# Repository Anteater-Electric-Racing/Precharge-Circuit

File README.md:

# [Schematic Preview](https://kicanvas.org/?github=https%3A%2F%2Fgithub.com%2FAnteater-Electric-Racing%2FPrecharge-Circuit%2Fblob%2Fmain%2Fpcc_v0.1.kicad_sch)

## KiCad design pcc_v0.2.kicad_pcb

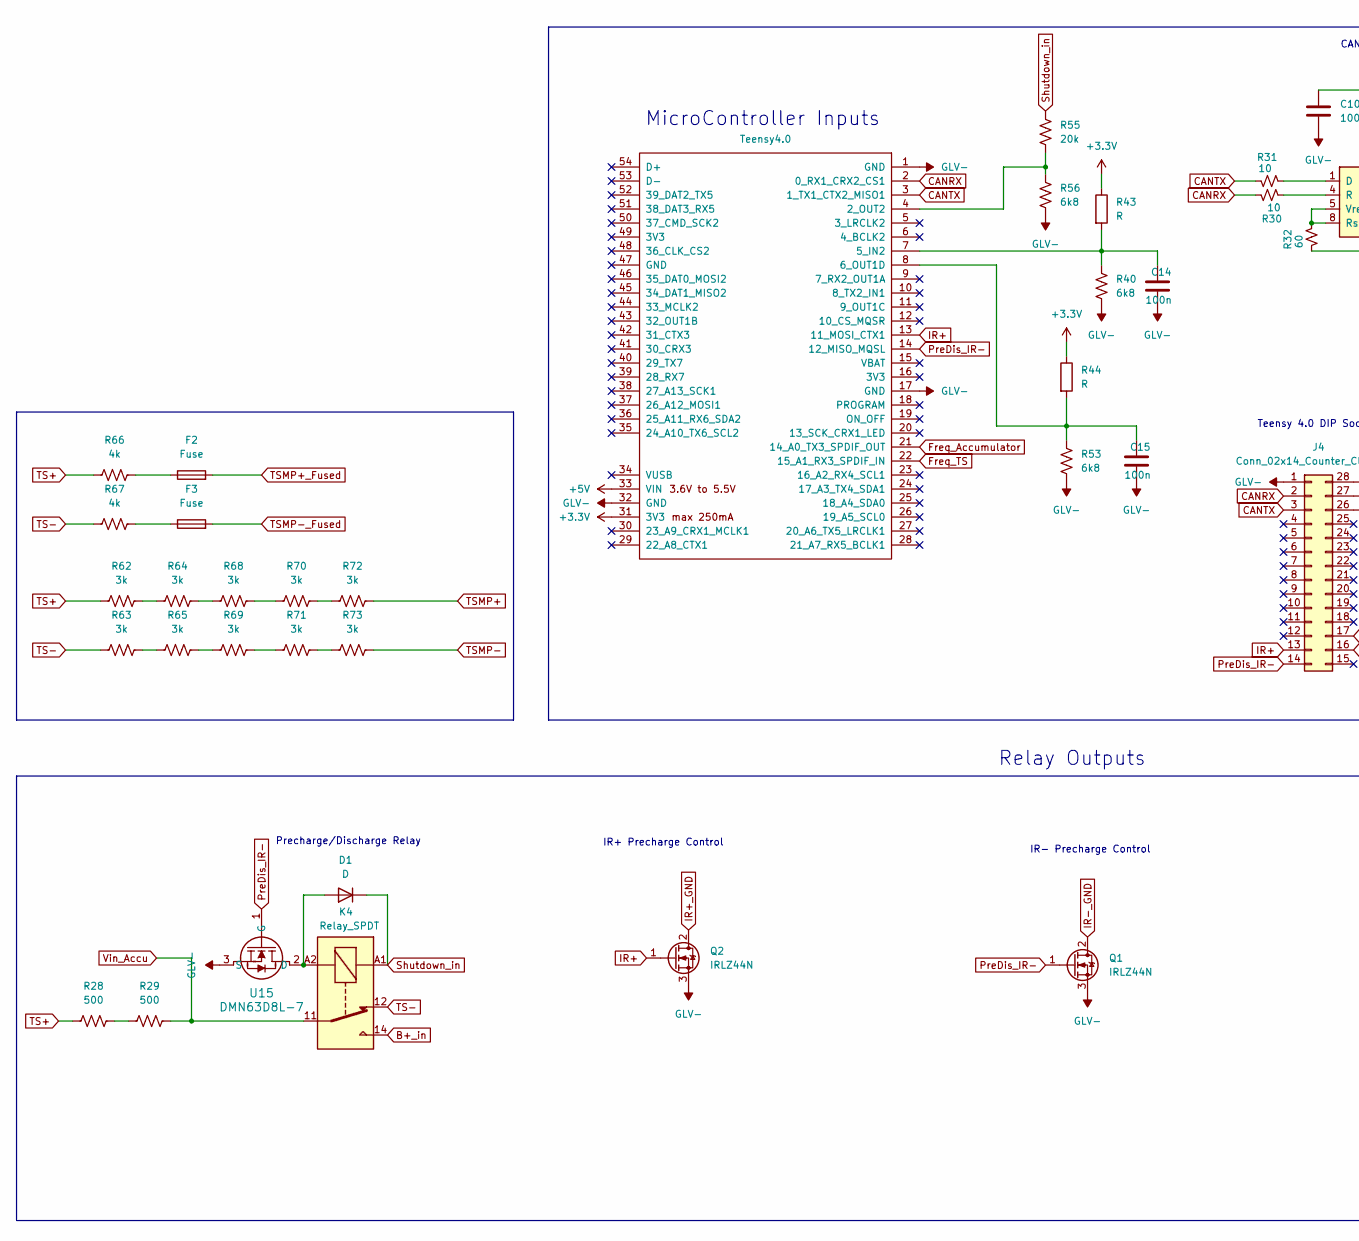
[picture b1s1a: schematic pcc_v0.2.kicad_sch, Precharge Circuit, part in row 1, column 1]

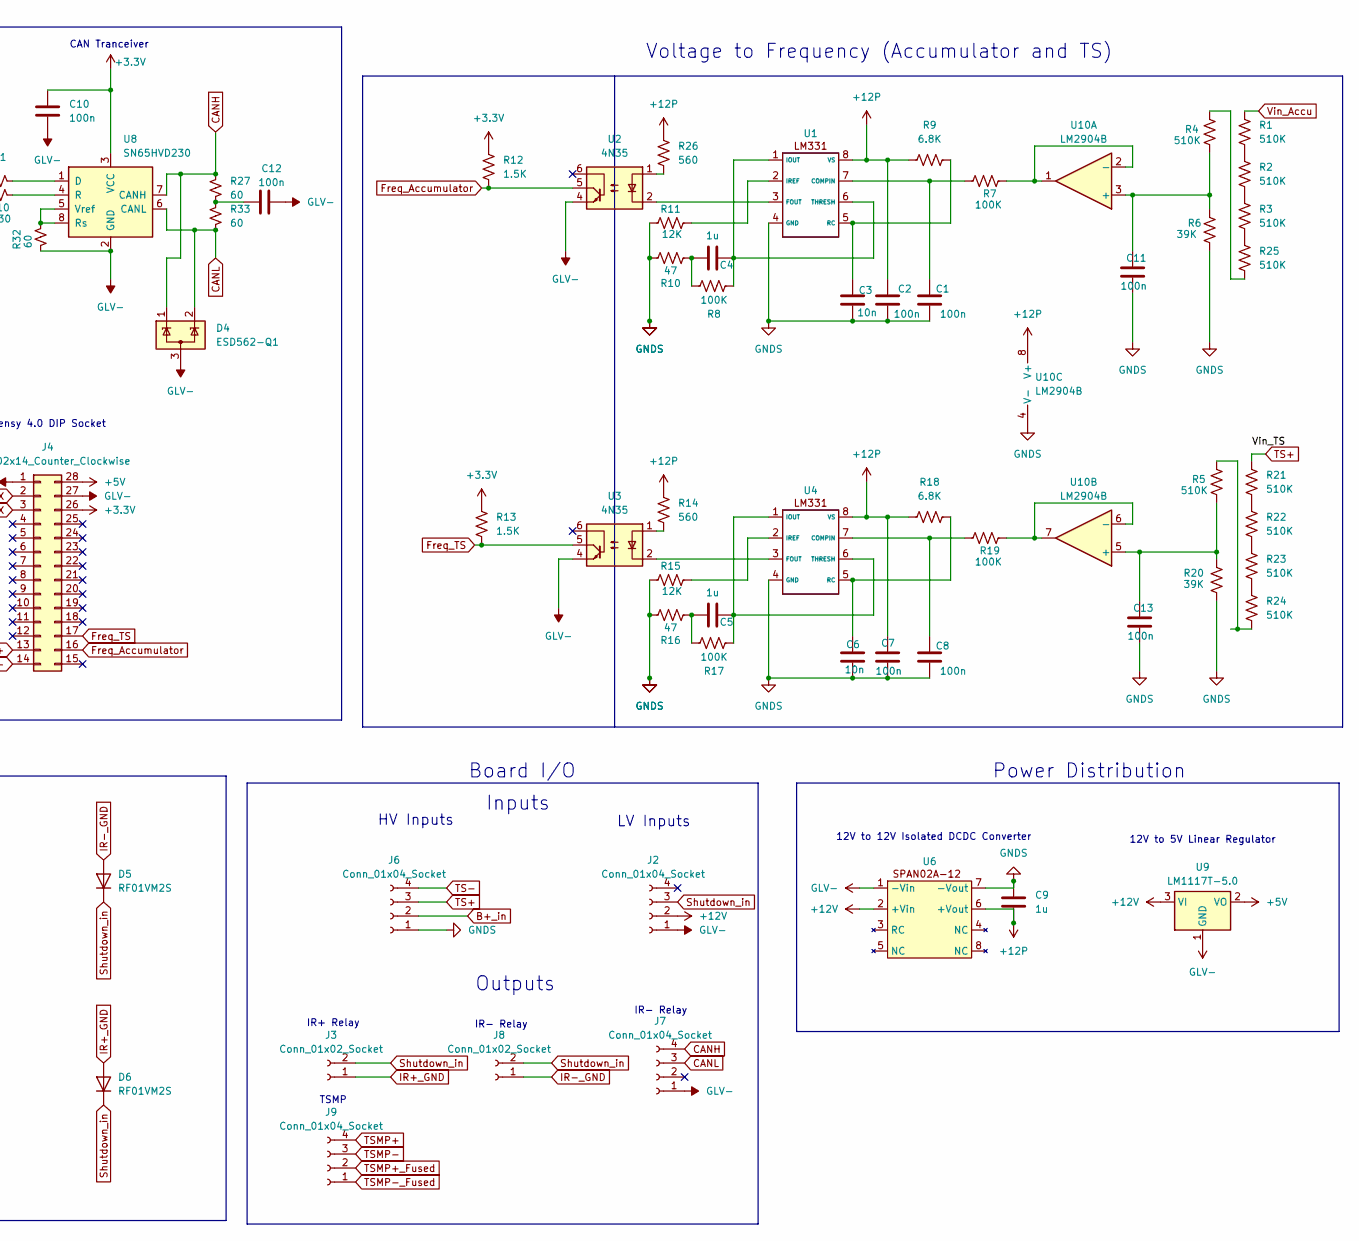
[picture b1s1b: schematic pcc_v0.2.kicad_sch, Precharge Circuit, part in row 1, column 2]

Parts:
C1, C2, C7, C8, C10, C11, C12, C13, C14, C15: 100n; C_0805_2012Metric
C3, C6: 10n; C_0805_2012Metric
C4, C5, C9: 1u; C_0805_2012Metric
D1: D; D_5KPW_P7.62mm_Vertical_AnodeUp
D4: ESD562-Q1; SOT-23-3
D5, D6: RF01VM2S; D_SOD-323
F2, F3: Fuse; Fuse_1206_3216Metric
J2, J6, J7, J9: Conn_01x04_Socket; Molex_Mini-Fit_Jr_5566-04A2_2x02_P4.20mm_Vertical
J3, J8: Conn_01x02_Socket; Molex_Mini-Fit_Jr_5566-02A2_2x01_P4.20mm_Vertical
J4: Conn_02x14_Counter_Clockwise; DIP-28_W15.24mm_Socket
K4: Relay_SPDT; Precharge_Discharge_Relay
Q1, Q2: IRLZ44N; TO-220-3_Vertical
R1, R2, R3, R4, R5, R21, R22, R23, R24, R25: 510K; R_0805_2012Metric
R6, R20: 39K; R_0805_2012Metric
R7, R8, R17, R19: 100K; R_0805_2012Metric
R9, R18: 6.8K; R_0805_2012Metric
R10, R16: 47; R_0805_2012Metric
R11, R15: 12K; R_0805_2012Metric
R12, R13: 1.5K; R_0805_2012Metric
R14, R26: 560; R_0805_2012Metric
R27, R32, R33: 60; R_0805_2012Metric
R28, R29: 500; Ohmite HS100 500R F
R30, R31: 10; R_0805_2012Metric
R40, R53, R56: 6k8; R_0805_2012Metric
R43, R44: R; PinSocket_1x02_P2.00mm_Vertical
R55: 20k; R_0805_2012Metric
R62, R63, R64, R65, R68, R69, R70, R71, R72, R73: 3k; R_2512_6332Metric
R66, R67: 4k; R_0805_2012Metric
U1, U4: DIP-8_W7.62mm_Socket
U2, U3: 4N35; DIP-6_W7.62mm_Socket
U6: SIP-8_19x3mm_P2.54mm
U7: Teensy4.0; DIP-28_W15.24mm_Socket
U8: SN65HVD230; SOIC-8_3.9x4.9mm_P1.27mm
U9: LM1117T-5.0; TO-220-3_Horizontal_TabDown
U10: LM2904B; SOIC-8_3.9x4.9mm_P1.27mm
U15: DMN63D8L-7; SOIC_63D8L-7_DIO

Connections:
+3.3V: C10.1, J4.26, R12.2, R13.2, R43.1, R44.1, U7.31 (3V3), U8.3 (VCC)
+5V: J4.28, U7.33 (VIN), U9.2 (VO)
+12P: C2.1, C7.1, C9.2, R9.1, R14.1, R18.1, R26.1, U1.8 (VS), U4.8 (VS), U6.6 (+Vout), U10.8 (V+)
+12V: J2.2, U6.2 (+Vin), U9.3 (VI)
B+_in: J6.2, K4.14
CANH: D4.1 (K), J7.4, R27.1, U8.7 (CANH)
CANL: D4.2 (K), J7.3, R33.2, U8.6 (CANL)
CANRX: J4.2, R30.1, U7.2 (0_RX1_CRX2_CS1)
CANTX: J4.3, R31.2, U7.3 (1_TX1_CTX2_MISO1)
Freq_Accumulator: J4.16, R12.1, U2.5, U7.21 (14_A0_TX3_SPDIF_OUT)
Freq_TS: J4.17, R13.1, U3.5, U7.22 (15_A1_RX3_SPDIF_IN)
GLV-: C10.2, C12.2, C14.2, C15.2, D4.3 (A), J2.1, J4.1, J4.27, J7.1, Q1.3 (S), Q2.3 (S), R32.2, R40.2, R53.2, R56.2, U2.4, U3.4, U6.1 (-Vin), U7.1 (GND), U7.17 (GND), U7.32 (GND), U8.2 (GND), U9.1 (GND), U15.3 (S)
GNDS: C1.2, C2.2, C3.2, C6.2, C7.2, C8.2, C9.1, C11.2, C13.2, J6.1, R6.2, R10.2, R11.1, R15.1, R16.2, R20.2, U1.4 (GND), U4.4 (GND), U6.7 (-Vout), U10.4 (V-)
IR+: J4.13, Q2.1 (G), U7.13 (11_MOSI_CTX1)
IR+_GND: D6.2 (A), J3.1, Q2.2 (D)
IR-_GND: D5.2 (A), J8.1, Q1.2 (D)
unnamed: C4.1, R8.1, R10.1
unnamed: C5.1, R16.1, R17.1
unnamed: C12.1, R27.2, R33.1
unnamed: C14.1, R40.1, R43.2, U7.7 (5_IN2)
unnamed: C15.1, R44.2, R53.1, U7.8 (6_OUT1D)
unnamed: D1.2 (A), K4.A2, U15.2 (D)
unnamed: F2.1, R66.1
unnamed: F3.1, R67.1
unnamed: R1.2, R2.1
unnamed: R2.2, R3.1
unnamed: R14.2, U3.1
unnamed: R21.2, R22.1
unnamed: R22.2, R23.1
unnamed: R23.2, R24.1
unnamed: R5.1, R24.2
unnamed: R3.2, R25.1
unnamed: R4.1, R25.2
unnamed: R26.2, U2.1
unnamed: R28.2, R29.1
unnamed: R55.2, R56.1, U7.4 (2_OUT2)
unnamed: R62.2, R64.1
unnamed: R63.2, R65.1
unnamed: R64.2, R68.1
unnamed: R65.2, R69.1
unnamed: R68.2, R70.1
unnamed: R69.2, R71.1
unnamed: R70.2, R72.1
unnamed: R71.2, R73.1
unnamed: C1.1, R7.1, U1.7 (COMPIN)
unnamed: U1.3 (FOUT), U2.2
unnamed: C4.2, R8.2, U1.1 (IOUT), U1.6 (THRESH)
unnamed: R11.2, U1.2 (IREF)
unnamed: C3.1, R9.2, U1.5 (RC)
unnamed: C8.1, R19.1, U4.7 (COMPIN)
unnamed: U3.2, U4.3 (FOUT)
unnamed: C5.2, R17.2, U4.1 (IOUT), U4.6 (THRESH)
unnamed: R15.2, U4.2 (IREF)
unnamed: C6.1, R18.2, U4.5 (RC)
unnamed: R31.1, U8.1 (D)
unnamed: R30.2, U8.4 (R)
unnamed: R32.1, U8.5 (Vref), U8.8 (Rs)
unnamed: C11.1, R4.2, R6.1, U10.3 (+)
unnamed: R7.2, U10.1, U10.2 (-)
unnamed: C13.1, R5.2, R20.1, U10.5 (+)
unnamed: R19.2, U10.6 (-), U10.7
PreDis_IR-: J4.14, Q1.1 (G), U7.14 (12_MISO_MQSL), U15.1 (G)
Shutdown_in: D1.1 (K), D5.1 (K), D6.1 (K), J2.3, J3.2, J8.2, K4.A1, R55.1
TS+: J6.3, R21.1, R28.1, R62.1, R66.2
TS-: J6.4, K4.12, R63.1, R67.2
TSMP+: J9.4, R72.2
TSMP+_Fused: F2.2, J9.2
TSMP-: J9.3, R73.2
TSMP-_Fused: F3.2, J9.1
Vin_Accu: K4.11, R1.1, R29.2

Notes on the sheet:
Board I/O
TSMP
HV Inputs
Inputs
IR+ Relay
LV Inputs
Teensy 4.0 DIP Socket
IR- Precharge Control
Voltage to Frequency (Accumulator and TS)
MicroController Inputs
IR- Relay
Relay Outputs
CAN Tranceiver
Precharge/Discharge Relay
IR+ Precharge Control
Outputs
Power Distribution
12V to 5V Linear Regulator
12V to 12V Isolated DCDC Converter

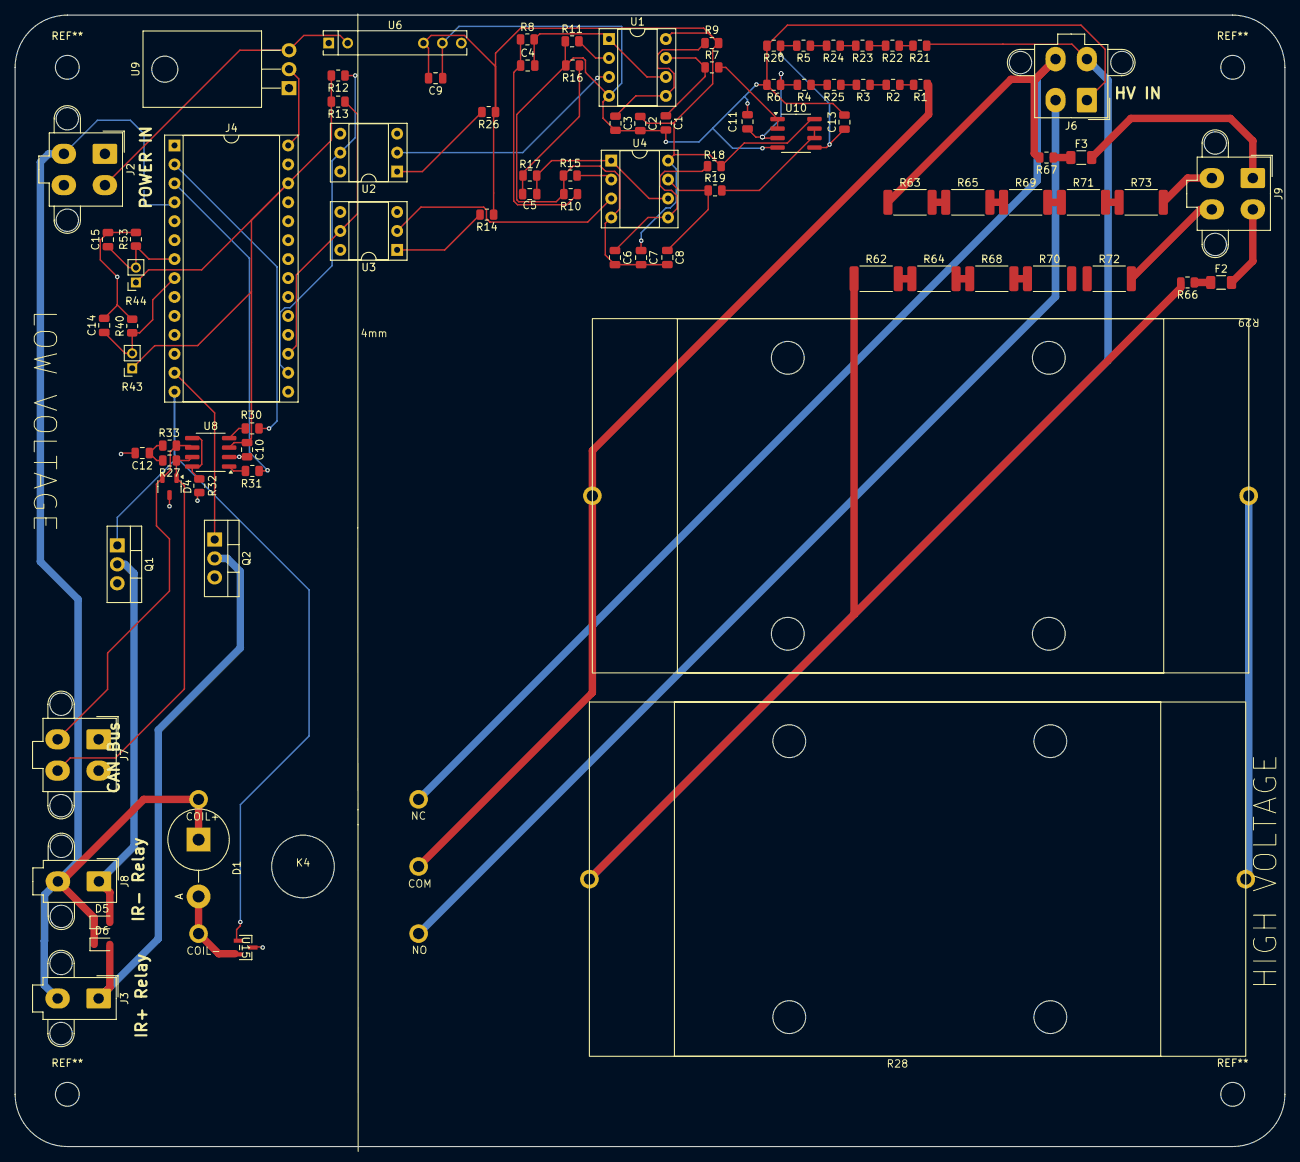
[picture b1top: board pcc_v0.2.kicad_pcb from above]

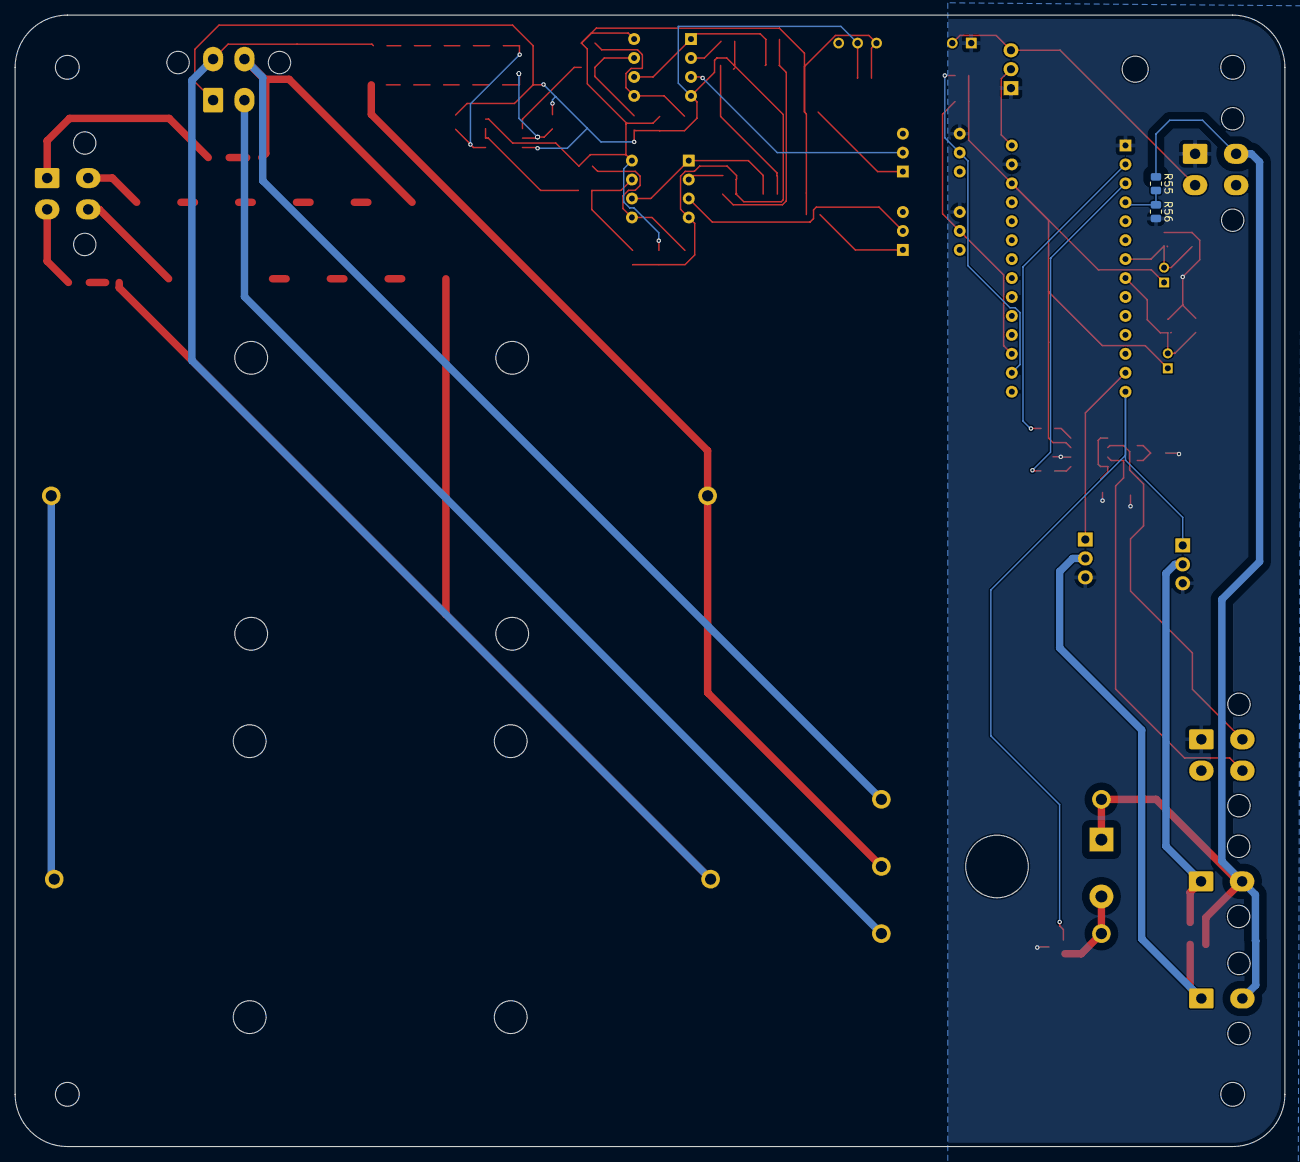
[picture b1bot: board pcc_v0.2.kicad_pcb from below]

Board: 2 copper layers, 170.3 x 151.7 mm, 91 parts (2 on the bottom side), 70 nets.

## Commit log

2024-12-03 pcc merge inputs and v-f
2024-12-03 Update schematic preview in readme
2024-12-05 Update README.md with image file
2024-12-05 add img preview
2024-12-05 show LV/HV isolation
2025-01-23 pcc modifications
2025-01-24 started pcb layout
2025-01-26 polishing layout
2025-01-27 cleaned up layout
2025-01-28 revised with all relay outputs
2025-01-29 looking to add discharge relay
2025-02-01 routed pcb
2025-02-10 next round of changes with correct precharge resistor and isolation distance
2025-02-12 next round of edits
2025-02-13 can tranceiver filtering stuff
2025-02-13 added discharge relay
2025-02-13 fixed text placement
2025-02-14 generated bom
2025-02-18 generated gerbers
2025-05-15 made custom footprint for relay. need to measure actual size
2025-05-16 corrected relay footprint, added flyback diode
2025-05-17 changed diode to tht and added connector labels
2025-05-17 regenerated gerbers
2025-05-20 updated schem
2025-06-03 made changes based on picture of working breadboard
2025-11-03 update git
2026-01-10 Add PCC version 2
2026-03-04 Removed v1
